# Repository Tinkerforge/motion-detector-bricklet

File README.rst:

Motion Detector Bricklet
========================

This repository contains the firmware source code and the hardware design
files. The documentation generator configs can be found at
https://github.com/Tinkerforge/generators

Repository Content
------------------

software/:
 * examples/: Examples for all supported languages
 * build/: Compiled files
 * src/: Source code of firmware
 * Makefile: Makefile to build project

hardware/:
 * Contains KiCad project files and additionally schematics as PDF

datasheets/:
 * Contains datasheets for sensors and complex ICs that are used

Hardware
--------

The hardware is designed with the open source EDA Suite KiCad
(http://www.kicad.org). Before you are able to open the files,
you have to install the Tinkerforge kicad-libraries
(https://github.com/Tinkerforge/kicad-libraries). You can either clone
them directly in hardware/ or clone them in a separate folder and
symlink them into hardware/
(ln -s kicad_path/kicad-libraries project_path/hardware). After that you
can open the .pro file in hardware/ with KiCad and from there view and
modify the schematics and the PCB layout.

Software
--------

If you want to do your own Brick/Bricklet firmware development we highly
recommend that you use our build environment setup script and read the
tutorial (https://www.tinkerforge.com/en/doc/Tutorials/Tutorial_Build_Environment/Tutorial.html).

To compile the C code we recommend you to install the newest GNU Arm Embedded
Toolchain (https://launchpad.net/gcc-arm-embedded/+download).
You also need to install bricklib (https://github.com/Tinkerforge/bricklib)
and brickletlib (https://github.com/Tinkerforge/brickletlib).

You can either clone it directly in software/src/ or clone it in a
separate folder and symlink it into software/src/
(ln -s bricklib_path/bricklib project_path/software/src/ and
ln -s brickletlib_path/brickletlib project_path/software/src/).
Finally make sure to have CMake installed
(http://www.cmake.org/cmake/resources/software.html).

After that you can build the firmware by invoking make in software/.
The firmware (.bin) can then be found in software/build/ and uploaded
with brickv (click button "Flashing" on start screen).

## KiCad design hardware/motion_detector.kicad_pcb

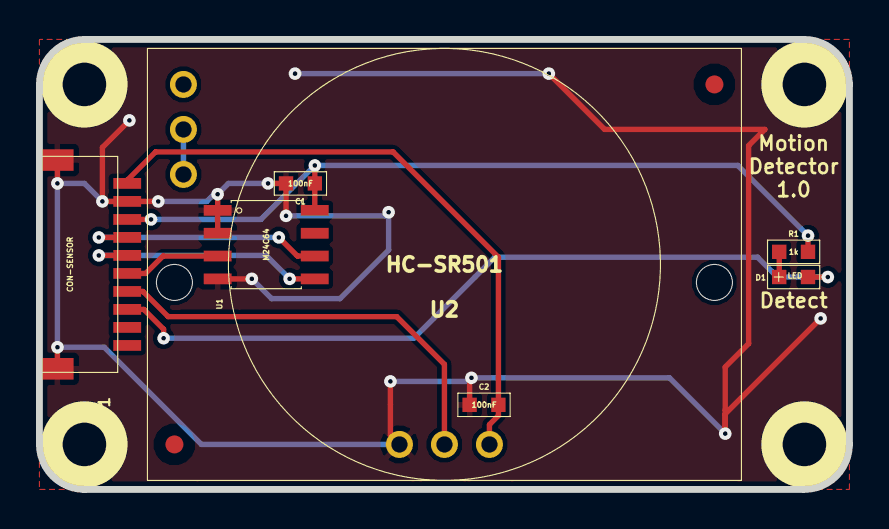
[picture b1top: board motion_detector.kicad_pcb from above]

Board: 2 copper layers, 45.0 x 25.0 mm, 15 parts (0 on the bottom side), 10 nets.

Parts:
C1, C2: 100nF; 0603
D1: LED; D0603
Fiducial_Mark: VAL**; Fiducial_Mark
Fiducial_Mark#2: VAL**; Fiducial_Mark
P1: CON-SENSOR
R1: 1k; 0603
U1: M24C64; SOIC8
U2: HC-SR501
U3, U4, U5, U6: DRILL; DRILL_NP
VAL: WEEE_7mm
VAL#2: CE_5mm

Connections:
+5V: C2.2, P1.1, U2.6
GND: C1.2, C2.1, P1.2, P1.EP, U1.1, U1.2, U1.4, U2.4
unnamed: P1.7, U2.5
unnamed: U2.2, U2.3
unnamed: P1.6, U1.3
unnamed: D1.2, P1.8
unnamed: D1.1, R1.1
unnamed: P1.4, U1.6
unnamed: P1.5, U1.5
VCC: C1.1, P1.3, R1.2, U1.8

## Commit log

2013-07-30 Initial commit for Motion Detector firmware
2013-07-31 Add prototype disclaimer to readme
2013-08-21 windows: Don't trigger a build in generate_makefile.bat
    Also use normal make instead of a special named one.
2013-09-17 Change debounce time to 50ms
2013-09-17 Add examples for Motion Detector Bricklet
2013-09-24 Swap values for motion, so it feels more like a bool value
2013-09-24 Control LED according to detection cycle
2013-10-15 add hardware files
2013-10-18 Fix name to fit naming standard
2013-10-18 Use correct file as schematic
2014-01-06 Add static assert for BrickContext size
2014-01-10 Add Perl examples
2014-01-10 Comment fixed: cb_detection_cycle_ended
2014-01-15 php: Use const for constant values
2014-02-07 Add Mathematica examples
2014-02-10 perl: fixed namespace
2014-02-18 javascript: examples fixed
2014-02-20 javascript: adding html examples
2014-02-24 javascript: port 4280, startExample()
2014-02-28 javascript: Break long lines and cleanup whitespace
2014-03-05 Add LabVIEW example
2014-03-06 labview: Add example in LV2010 format
2014-03-26 matlab: add examples
2014-04-02 java: Unify constants style
2014-04-02 perl: Unify print style
2014-04-17 matlab: Adapt examples to new callback style
2014-04-17 matlab: Add parentheses to make pygments happy
2014-07-15 java: Replace System.console() usage with an Eclipse compatible pattern
2014-12-02 Use ReadLine instead of ReadKey for C# example
2014-12-04 remove big silkscreen lines
2014-12-15 fix text position
2015-02-13 vbnet: Use ReadLine instead of ReadKey
    Because ReadKey doesn't work with a pipe as stdin on the RED Brick.
2015-03-02 windows: Stop cmake from searching for mingw32-make.exe
    Using MinGW Makefiles as generator makes cmake search for mingw32-make.exe
    which might not be installed because GnuWin32's make.exe is used instead.
2015-06-24 javascript: Clean up output creation
2015-07-25 Make JavaScript browser example textarea readonly
2015-07-27 Cleanup C/C++, C#, Java, Python and Ruby examples
2015-07-29 Reformat changelog
2015-08-07 Use full device class name in Python examples
2015-08-12 Fix minor warnings in C/C++ examples
2015-08-17 Whitespace
2015-08-18 Add missing comment in VB.NET example
2015-08-19 Cleanup Perl example
2015-09-09 Duplicate cmake call to fix bug during cmake creation
2015-09-30 Generator based example cleanup
2015-11-12 matlab: Fix callback handling for R2014a
    http://undocumentedmatlab.com/blog/matlab-callbacks-for-java-events-in-r2014a
2015-11-25 Include date and commit into changelog
2016-05-18 c: Add missing device destroy call
2016-07-01 Make the change UID comment more explicit
2016-08-04 fix plane outlines
2016-08-09 fix pcb name
2017-01-09 Add status LED configuration support
2017-01-09 Use Date/Version format in changelog
2017-01-16 Fix changelog
2017-04-13 csharp: Adapt example
2017-06-02 octave: Use javaObject instead of deprecated java_new
2017-11-30 Update examples from generator
2017-12-07 mathematica: Also generate .nb files
2018-02-19 javascript: Close div tag correctly
2018-02-20 Cleanup KiCad libraries config
    Ensure LibDir=kicad-libraries and LibName1=tinkerforge.
    Remove special library.
2018-02-26 Add missing schematic
2018-05-24 perl: Use strict in examples
2018-07-11 Add Makefile with docker support
2018-07-11 Remove obsolete generate_makefile scripts
2018-07-11 Update directory structure and build instructions
2018-11-06 Add rust examples
2018-11-07 rust: Accept host names for ip connection, fix naming inconsistencies
2018-11-07 rust: Rename callback receivers.
2018-12-14 Add go examples.
2018-12-18 go: Change import path.
2018-12-18 go: Change import path again.
2018-12-20 rust: Reformat examples.
2019-01-24 mqtt: Add examples.
2019-01-24 mqtt: Fix example header.
2019-01-24 mqtt: Remove executable bit in example permissions.
2019-01-24 go: Minor example fixes.
2019-01-24 mqtt: Minor example fixes.
2019-05-14 Update rust examples.
2019-08-22 c: Adapt to bindings changes
2020-01-13 examples: Use python3 input instead of python2 raw_input.
2020-01-13 examples: mqtt: Remove trailing whitespace.
2021-10-25 Update KiCad link
    https://www.kicad.org/blog/2021/10/Avoid-links-to-former-kicad-domain/
2022-07-06 Add license files.

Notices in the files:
hardware/motion_detector.kicad_pcb:
Licensed under CERN OHL v.1.1
Copyright (©) 2013, B.Nordmeyer
Copyright Tinkerforge GmbH 2013.
This documentation describes Open Hardware and is licensed under the
CERN OHL v. 1.1.
